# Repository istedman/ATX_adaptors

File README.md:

# ATX_adaptors
ATX power adaptors for the Amiga and other retro computers. Allows easy access to an ATX replacement supply. The +5V, +12V and -12C supplies are available on screw terminal connectors for easy retro fit. The Multi-purpose design can also supply -5V, the 50/60Hz tick signal and a Power_good signal.

The schematics and PCB files are included here in Eagle CAD format, V7 or later is required to open the files.

The adaptors use a Microchip PIC10F200 microcontroller to debounce the switch and to turn on/off the power. The same micro is used to provide a 50/60Hz 'tick' signal. Accuracy was ~0.5Hz using internal oscillator. A Tag-connect MCP2030 is required to program the device. The ATX_PICV1.zip file has the software. MplabX and XC8 compiler required to rebuild. A hex file is within the archive.

# 2021 Update

I'm discontinuing sales of all Amiga related projects. Reduced order volumes and extra issues with order post Brexit have not made it viable to continue.
All information, including BOMs, Gerbers and notes are now in the repository, if you want to build your own.

# 2025 update

I have re-exported the BOM data from the Excel originals. The part numbers are those from Quick-teck, who used to manufacture these boards for me. It's not a complicated design.

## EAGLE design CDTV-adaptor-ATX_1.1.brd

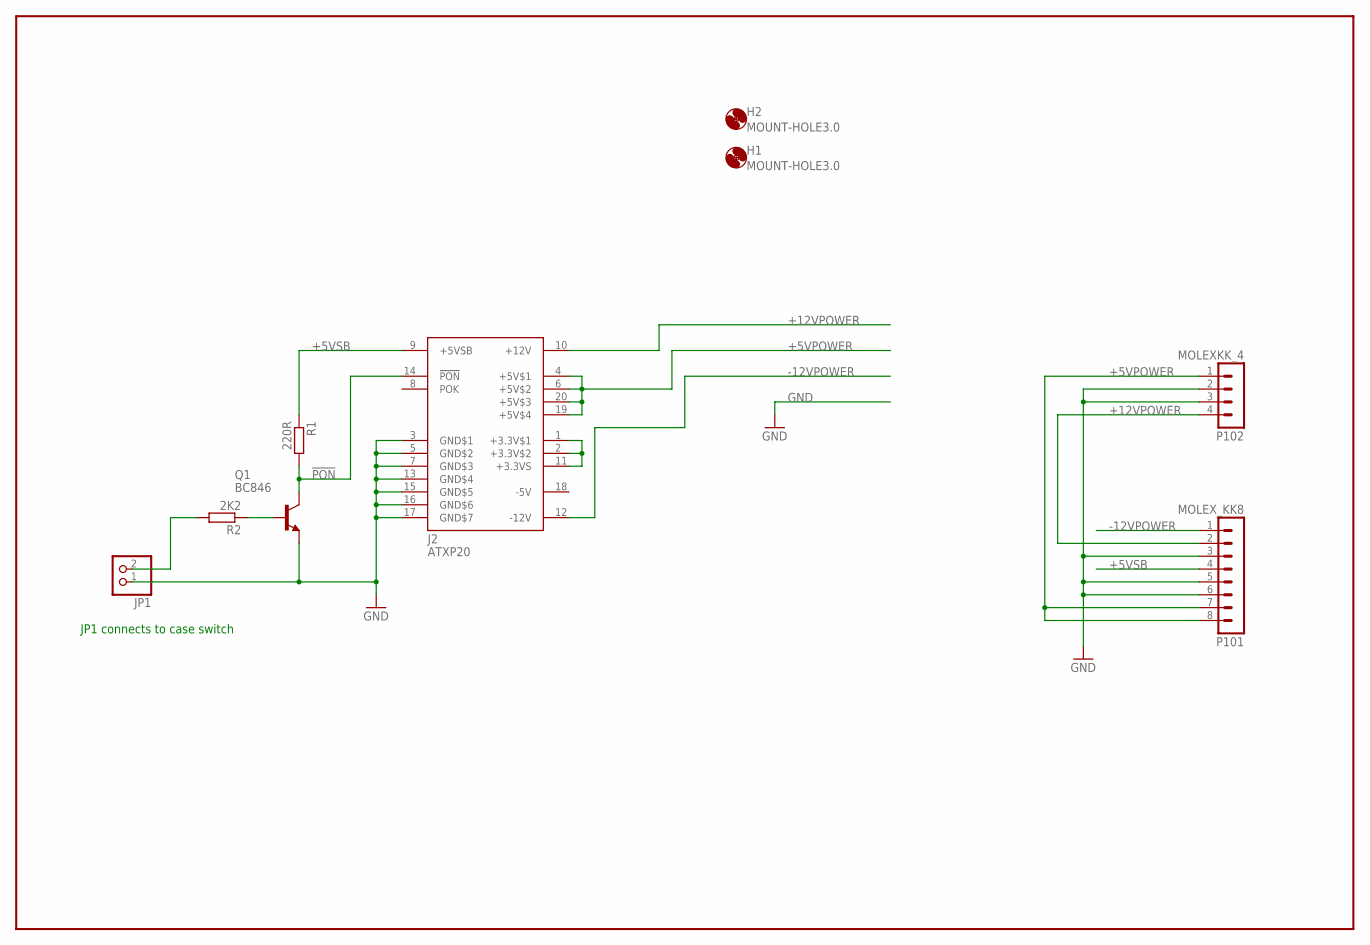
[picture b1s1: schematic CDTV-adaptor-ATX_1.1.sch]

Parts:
H1, H2: MOUNT-HOLE3.0; 3,0
J2: ATXP20; MOLEX39281203
JP1: PINHD-1X2; 1X02
P101: MOLEX_KK8
P102: MOLEXKK_4; MA04-1
Q1: BC846; SOT23
R1: 220R; R0603
R2: 2K2; R0603

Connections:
!PON: J2.14 (!PON), Q1.3 (C), R1.2
+5VPOWER: J2.4 (+5V$1), J2.6 (+5V$2), J2.19 (+5V$4), J2.20 (+5V$3), P101.7, P101.8, P102.1
+5VSB: J2.9 (+5VSB), P101.4, R1.1
+12VPOWER: J2.10 (+12V), P101.2, P102.4
-5V: J2.18 (-5V)
-12VPOWER: J2.12 (-12V), P101.1
GND: J2.3 (GND$1), J2.5 (GND$2), J2.7 (GND$3), J2.13 (GND$4), J2.15 (GND$5), J2.16 (GND$6), J2.17 (GND$7), JP1.1, P101.3, P101.5, P101.6, P102.2, P102.3, Q1.2 (E)
unnamed: Q1.1 (B), R2.1
unnamed: J2.1 (+3.3V$1), J2.2 (+3.3V$2), J2.11 (+3.3VS)
SWITCH: JP1.2, R2.2

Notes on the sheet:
JP1 connects to case switch

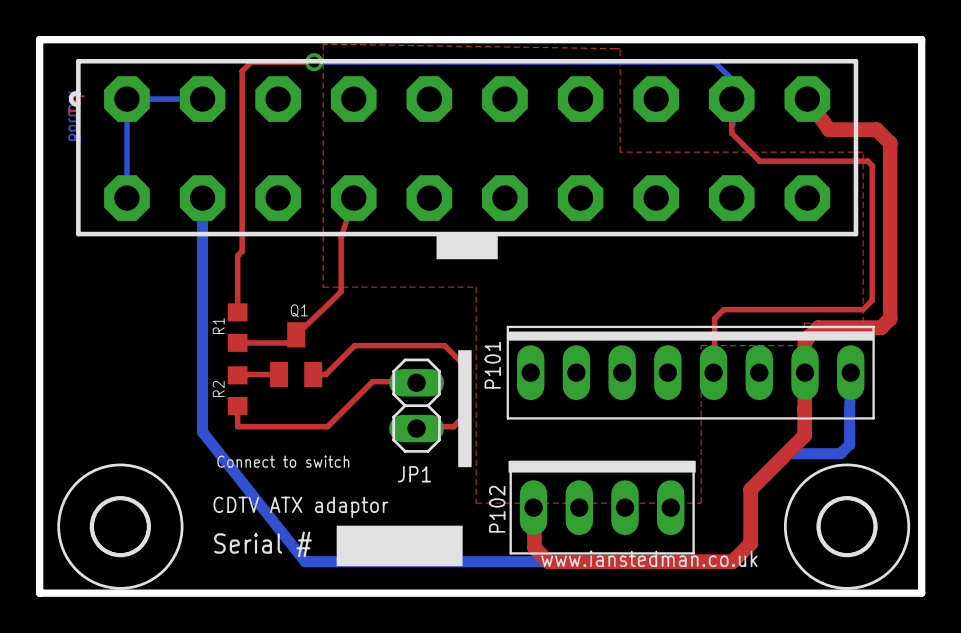
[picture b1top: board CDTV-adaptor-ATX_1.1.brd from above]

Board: 2 copper layers, 49.0 x 30.8 mm, 9 parts (0 on the bottom side), 9 nets.

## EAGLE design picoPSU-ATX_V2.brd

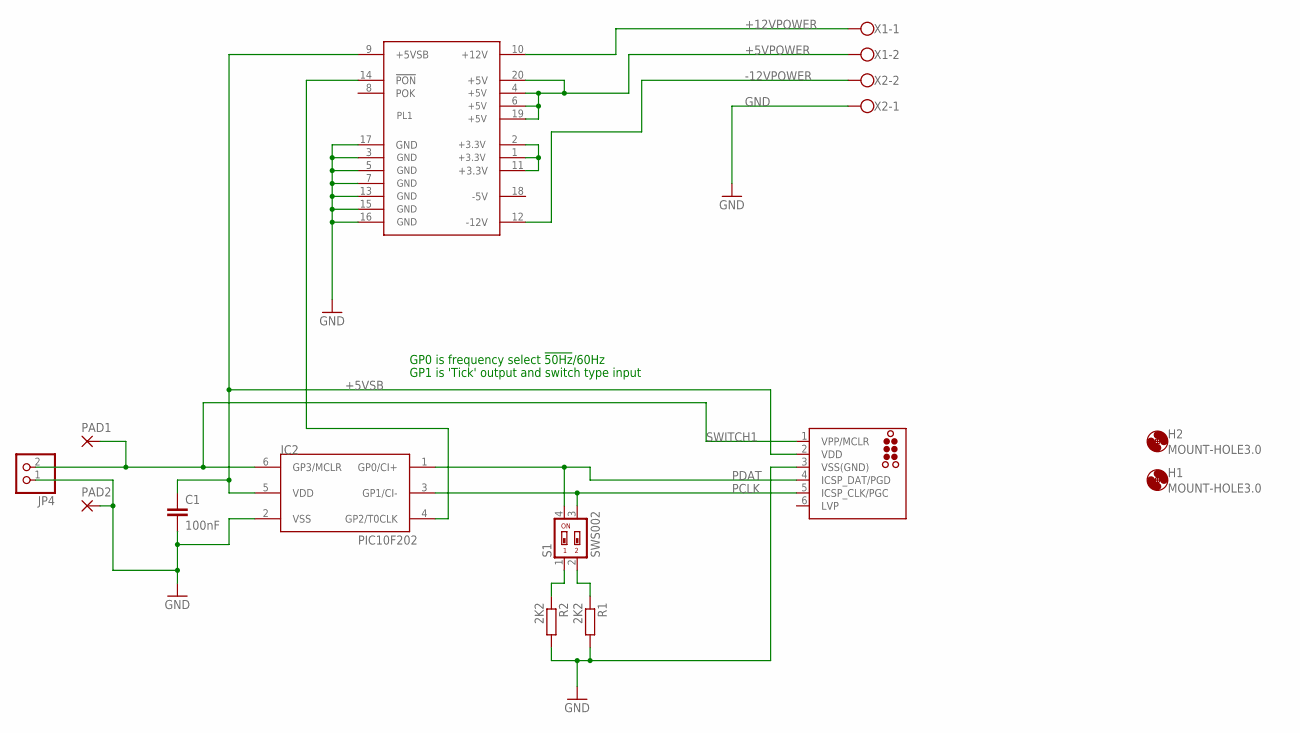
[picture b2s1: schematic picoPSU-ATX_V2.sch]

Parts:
C1: 100nF; C0805
H1, H2: MOUNT-HOLE3.0; 3,0
IC2: PIC10F202; SOT23-6
J1: TC2030-MCP-NL
JP4: PINHD-1X2; 1X02
PAD1, PAD2: 2,54/1,1
PL1: MOLEX39-30-1200; ATX_RIGHT
R1, R2: 2K2; R0603
S1: SWS002; SMS-002
X1, X2: W237-102

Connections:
+5VPOWER: PL1.4 (+5V), PL1.6 (+5V), PL1.19 (+5V), PL1.20 (+5V), X1.2
+5VSB: C1.1, IC2.5 (VDD), J1.2 (VDD), PL1.9 (+5VSB)
+12VPOWER: PL1.10 (+12V), X1.1
-12VPOWER: PL1.12 (-12V), X2.2
GND: C1.2, IC2.2 (VSS), J1.3 (VSS(GND)), JP4.1, PAD2.1, PL1.3 (GND), PL1.5 (GND), PL1.7 (GND), PL1.13 (GND), PL1.15 (GND), PL1.16 (GND), PL1.17 (GND), R1.2, R2.2, X2.1
unnamed: R2.1, S1.1
unnamed: R1.1, S1.2
unnamed: PL1.1 (+3.3V), PL1.2 (+3.3V), PL1.11 (+3.3V)
PCLK: IC2.3 (GP1/CI-), J1.5 (ICSP_CLK/PGC), S1.3
PDAT: IC2.1 (GP0/CI+), J1.4 (ICSP_DAT/PGD), S1.4
PWRON: IC2.4 (GP2/T0CLK), PL1.14 (!PON)
SWITCH1: IC2.6 (GP3/MCLR), J1.1 (VPP/MCLR), JP4.2, PAD1.1

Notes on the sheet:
GP0 is frequency select !50Hz!/60Hz
GP1 is 'Tick' output and switch type input

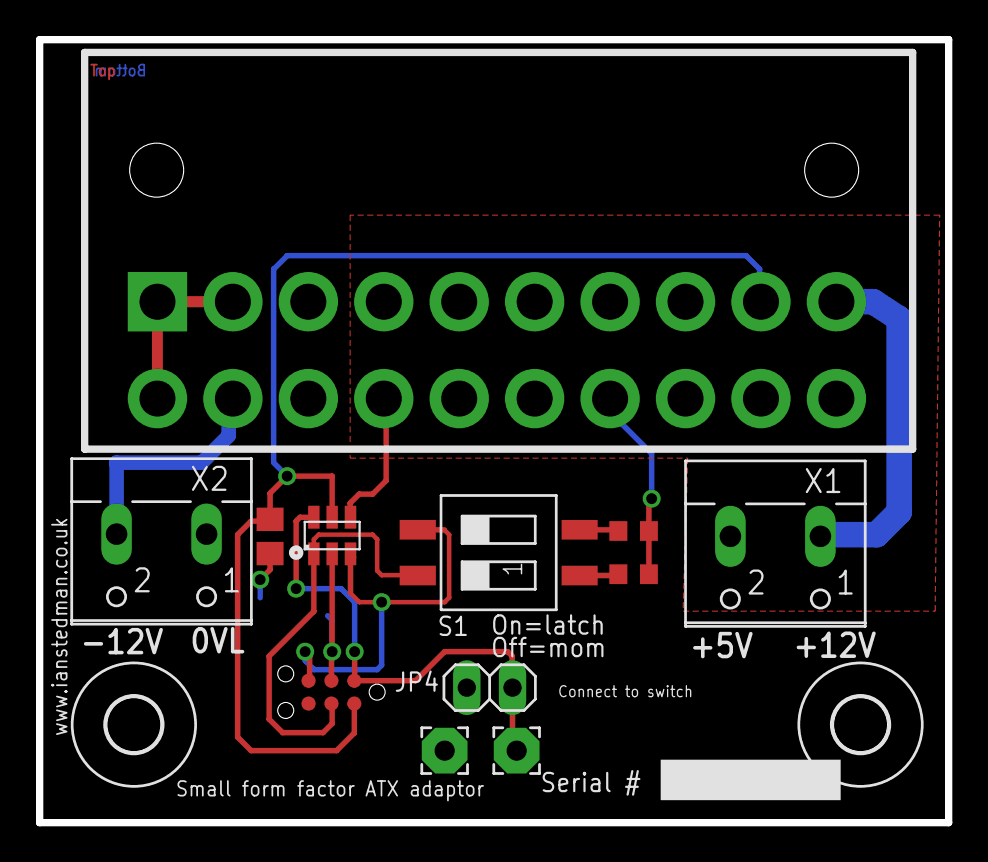
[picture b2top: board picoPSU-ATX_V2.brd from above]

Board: 2 copper layers, 50.5 x 43.5 mm, 14 parts (0 on the bottom side), 12 nets.

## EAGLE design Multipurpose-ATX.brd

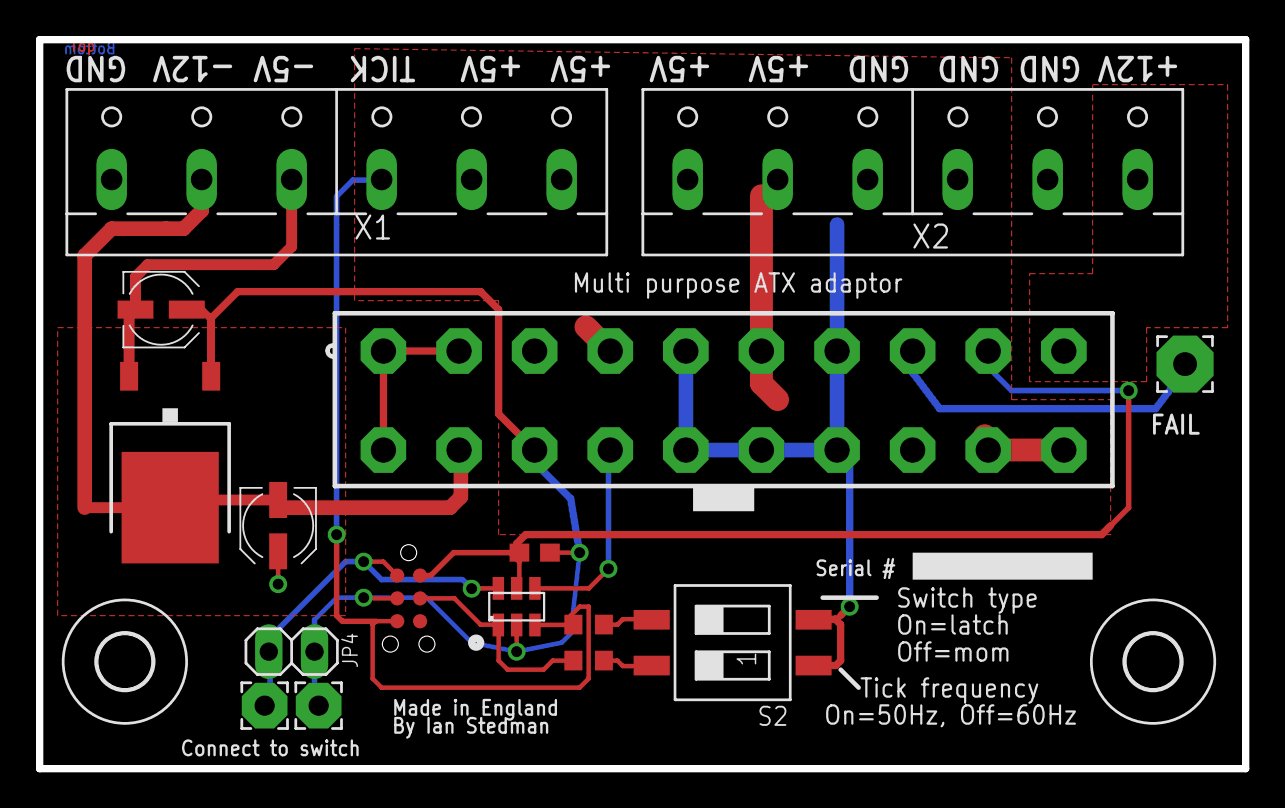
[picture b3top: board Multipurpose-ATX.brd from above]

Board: 2 copper layers, 67.0 x 40.5 mm, 18 parts (0 on the bottom side), 14 nets.

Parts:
C1: 100nF; C0603
C2: 1uF; UD-4X5,8_NICHICON
C3: 2.2uF; UD-4X5,8_NICHICON
FAIL: 3,17/1,3
H1, H2: MOUNT-HOLE3.0; 3,0
IC1: MC79M05CDTG; DPACK_3
IC2: PIC10F202; SOT23-6
J1: ATXP20; MOLEX39281203
J2: TC2030-MCP-NL
JP4: 1X02
PAD1, PAD2: 2,54/1,1
R1, R2: 2K2; R0603
S2: SWS002; SMS-002
X1, X2: W237-6

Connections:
+3V3: J1.1, J1.2, J1.11
+5VPOWER: J1.4, J1.6, J1.19, J1.20, X1.5, X1.6, X2.1, X2.2
+5VSB: C1.1, IC2.5, J1.9, J2.2
+12VPOWER: J1.10, X2.6
-12VPOWER: C2.-, IC1.4, J1.12, X1.2
FAIL: FAIL.1, J1.8
GND: C1.2, C2.+, C3.+, IC1.1, IC2.2, J1.3, J1.5, J1.7, J1.13, J1.15, J1.16, J1.17, J2.3, JP4.1, PAD2.1, S2.1, S2.2, X1.1, X2.3, X2.4, X2.5
unnamed: R2.2, S2.3
unnamed: R1.2, S2.4
unnamed: C3.-, IC1.3, X1.3
PCLK: IC2.3, J2.5, R2.1, X1.4
PDAT: IC2.1, J2.4, R1.1
PWRON: IC2.4, J1.14
SWITCH1: IC2.6, J2.1, JP4.2, PAD1.1

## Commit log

2017-08-01 Add files via upload
    Gerber files for the PCBs, these are the files I send to the PCB vendor.
2021-09-13 Add files via upload
    Export of BOMs from Excel based on the most recent build data.
2022-12-28 Add files via upload
    Fixed the software to compile with MPLAB 6/XC8
2022-12-28 Delete ATX_PIC_SW_V1.zip
    Out of date
2023-03-16 Add files via upload
    CDTV adaptor Gerber files
2023-03-16 Add files via upload
    Eagle CAD 7.7 original files for the CDTV adaptor
2025-05-29 Add files via upload
    Re-exported from the master spreadsheet, just a single page now.

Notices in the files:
parts and their libraries:
tag-connect: ©2009 ROFA.cz - modified and updated by Robert Darlington ‹rdarlington@gmail.com›
